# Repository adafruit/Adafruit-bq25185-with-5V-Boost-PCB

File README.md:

## Adafruit bq25185 USB - DC - Solar Charger with 5V Boost Board PCB

<a href="http://www.adafruit.com/products/6106"><br/>
Click here to purchase one from the Adafruit shop</a>

PCB files for the Adafruit bq25185 USB - DC - Solar Charger with 5V Boost Board. 

Format is EagleCAD schematic and board layout
* https://www.adafruit.com/product/6106

### Description

We're always on the look out for better ways to make projects portable: being able to charge your battery in the most convenient manner will let projects run no matter what power is available. Then we added a power supply chip with it to let you run your project without a separate board. The result is the Adafruit bq25185 USB / DC / Solar Charger with 5V Boost Board!

It uses the new bq25185 is a nifty charger chip with fairly high charge current, power path support, and the ability to charge from USB, DC or solar power. It's also a great value, so it's a good upgrade from MCP73833 or MCP73831-based charger boards. The boost converter is the TPS61023, which will give up to 1 Amp output with good efficiency, to squeeze the most power possible out of your battery.

This board is meant to be everything you need to power your 5V electronics: simply connect a 500mAh or larger battery to the JST PH 2-pin port, then charge it when you can from USB or DC/solar. At the other end is a terminal block which will provide the 5V output from the boost converter. 

* USB Type C connector with 5.1k CC resistors so it will work with any computer or power supply to get 5V and up to 1A. Data lines available if needed, on the bottom breakout.
* Separate DC or Solar Input - Two pads on the edge can be used to connect a 5 ~ 18V power supply, which can be used instead of USB. If the input is a solar panel, the charging chip will adjust the current draw so that the voltage does not dip below the battery, thus optimizing the solar power input. No large capacitor needed to stabilize it, and you get near-MPPT capability without the cost and complexity of MPPT.
* Default charge rate of 1A, but you can cut the jumper on the back to set the rate to 500mA
* Power Path to Load - If the 5V load connector is drawing current while the USB / DC/Solar power is attached, it will default to drawing current from the charger and any left over current will go to the battery. That keeps your battery from constantly charging/discharging which will reduce the battery life.
* Regulated 5V Output - a boost converter will take the load output from the bq25185 and convert it to 5V at 1 Amp max load. Note the TP61023 cannot turn on/off high loads, it will stall over 200mA. That means its not going to like it if you have a high current load that instantly draws full current on power up, like a resistive dummy load. The vast number of microcontroller projects will start up with <200mA and then a half second later will turn on high current items like LEDs, motors, wifi/radios, or displays so the restriction won't affect it.
* Three Status LEDs - Orange Charging LED, red Fault LED, and Green 3.3V output LED.
* Enable pad - to disable the 5V boost converter.
* Mounting holes!

This board is pretty much plug-and-play. Change the charging jumper if you like, then connect your battery to the BATT port, and the 5V output goes to your circuit. You can monitor the voltage on the battery via the secondary pads on the bottom edge, if necessary.

To use with solar, pick up a 5~7V solar panel (using a higher voltage panel will only lose the extra voltage as heat so there's no benefit to going over 7V), and either cut the connector off to wire it directly, or use a 2.1mm adapter cable plus a 2.1mm terminal block to get two wires for the DC Input port.

If you need a board with higher charge current or a DC plug already on-board, check out the bq24074 which has up to 1.5A charge rate and a on-board 2.1mm DC jack. It doesn't have a boost converter but you could wire up the TPS61023 separately

### License

Adafruit invests time and resources providing this open source design, please support Adafruit and open-source hardware by purchasing products from [Adafruit](https://www.adafruit.com)!

Designed by Limor Fried/Ladyada for Adafruit Industries.

Creative Commons Attribution/Share-Alike, all text above must be included in any redistribution. 
See license.txt for additional details.

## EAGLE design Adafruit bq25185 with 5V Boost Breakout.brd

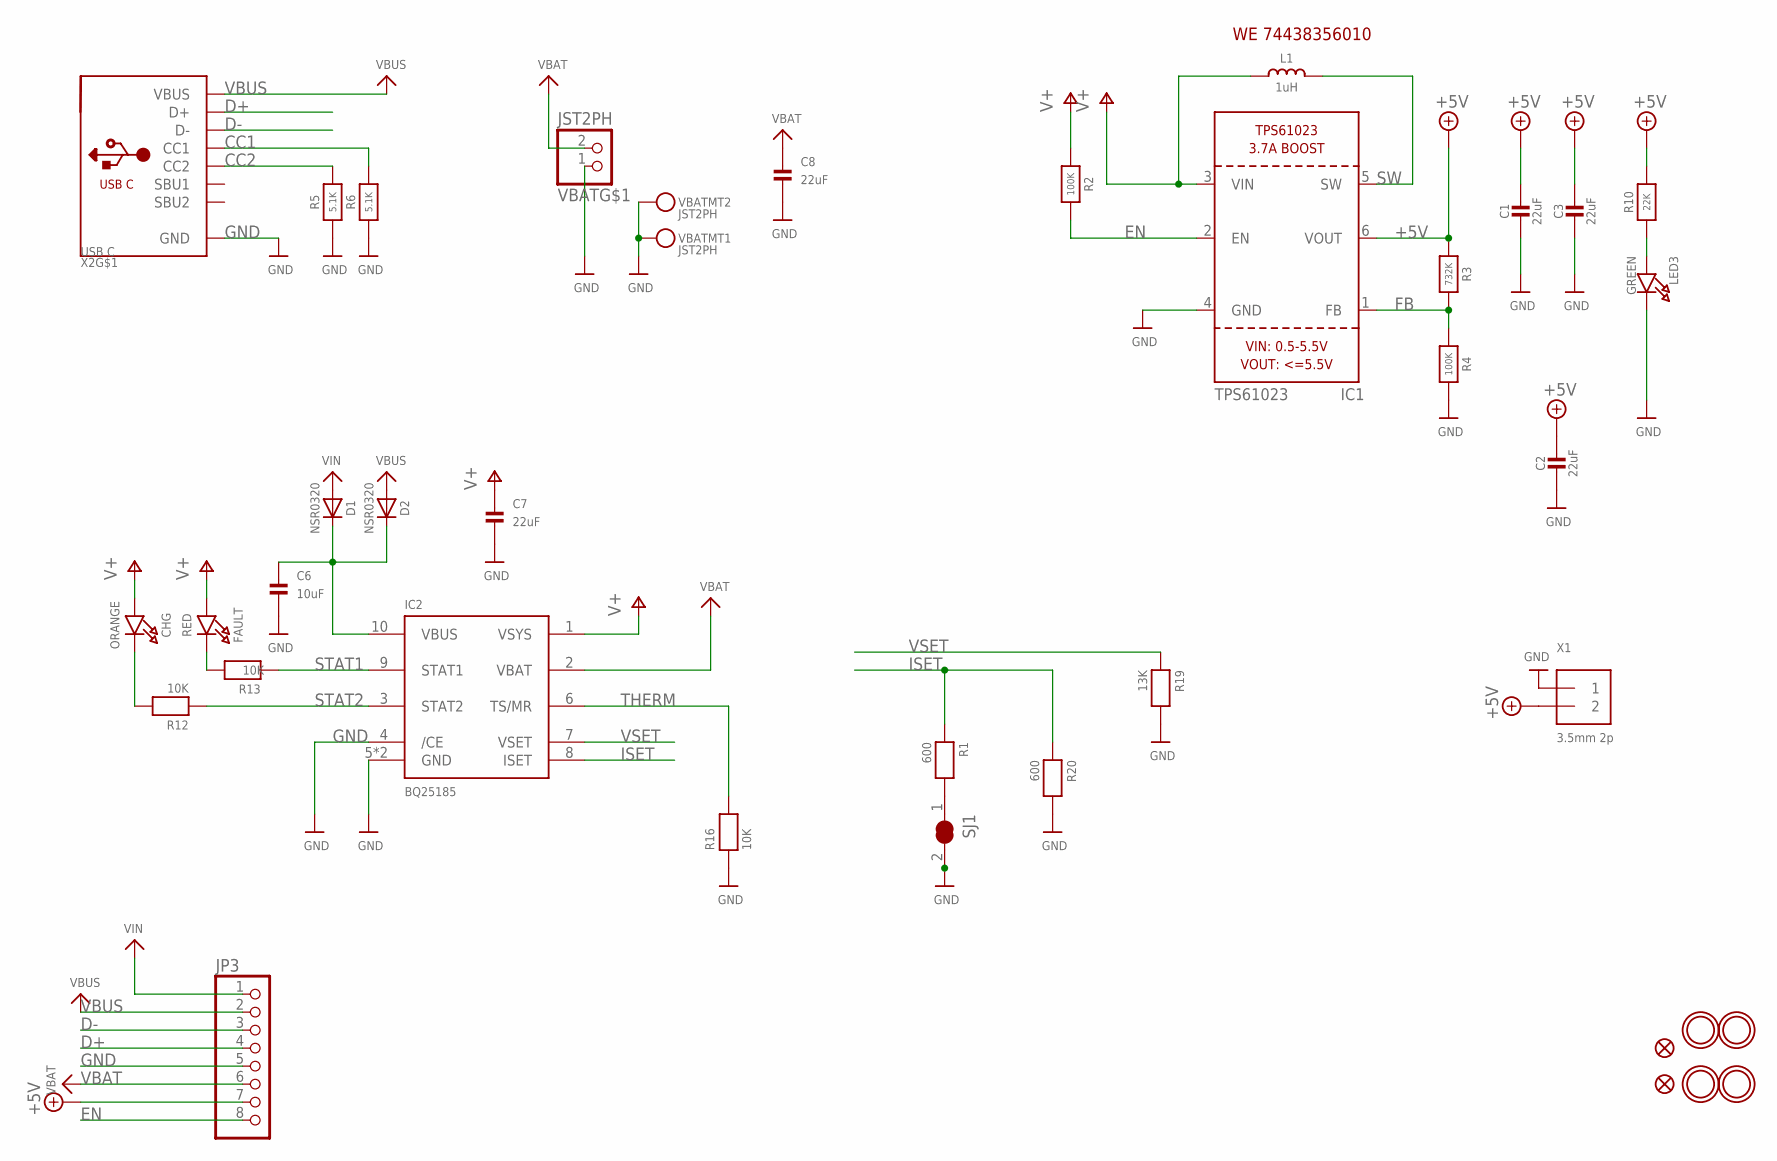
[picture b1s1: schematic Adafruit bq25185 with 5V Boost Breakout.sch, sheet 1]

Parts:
C1, C2, C3, C7, C8: 22uF; 0805-NO
C6: 10uF; 0805-NO
CHG: ORANGE; CHIPLED_0603_NOOUTLINE
D1, D2: NSR0320; SOD-323_MINI
FAULT: RED; CHIPLED_0603_NOOUTLINE
FID1, FID2: FIDUCIAL_0.5MM
IC1: TPS61023; SOT563
IC2: BQ25185; WSON10
JP3: HEADER-1X870MIL; 1X08_ROUND_70
L1: 1uH; INDUCTOR_5045_SMALLTABS
LED3: GREEN; CHIPLED_0603_NOOUTLINE
R1, R20: 600; _0402NO
R2, R4: 100K; _0402NO
R3: 732K; _0402NO
R5, R6: 5.1K; _0402NO
R10: 22K; _0402NO
R12, R13, R16: 10K; _0402NO
R19: 13K; _0402NO
SJ1: SOLDERJUMPER_CLOSED; SOLDERJUMPER_CLOSEDWIRE
U$9, U$10, U$11, U$12: MOUNTINGHOLE2.5; MOUNTINGHOLE_2.5_PLATED
VBAT: JST2PH; JSTPH2_BATT
X1: 3.5mm 2p; TERMBLOCK_1X2-3.5MM
X2: USB C; USB_C_CUSB31-CFM2AX-01-X

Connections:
+5V: C1.1, C2.1, C3.1, IC1.6 (VOUT), JP3.7, R3.1, R10.2, X1.2
CC1: R6.2, X2.A5 (CC1)
CC2: R5.2, X2.B5 (CC2)
D+: JP3.4, X2.A6 (D+), X2.B6 (D+)
D-: JP3.3, X2.A7 (D-), X2.B7 (D-)
EN: IC1.2 (EN), JP3.8, R2.2
FB: IC1.1 (FB), R3.2, R4.1
GND: C1.2, C2.2, C3.2, C6.2, C7.2, C8.2, IC1.4 (GND), IC2.4 (/CE), IC2.5 (GND), IC2.PAD (GND), JP3.5, LED3.C, R4.2, R5.1, R6.1, R16.1, R19.2, R20.2, SJ1.2, VBAT.1, VBAT.NC1, VBAT.NC2, X1.1, X2.A1B12 (GND), X2.B1A12 (GND)
ISET: IC2.8 (ISET), R1.1, R20.1
unnamed: R1.2, SJ1.1
unnamed: C6.1, D1.C, D2.C, IC2.10 (VBUS)
unnamed: CHG.C, R12.2
unnamed: LED3.A, R10.1
unnamed: FAULT.C, R13.2
STAT1: IC2.9 (STAT1), R13.1
STAT2: IC2.3 (STAT2), R12.1
SW: IC1.5 (SW), L1.2
THERM: IC2.6 (TS/MR), R16.2
V+: C7.1, CHG.A, FAULT.A, IC1.3 (VIN), IC2.1 (VSYS), L1.1, R2.1
VBAT: C8.1, IC2.2 (VBAT), JP3.6, VBAT.2
VBUS: D2.A, JP3.2, X2.A4B9 (VBUS), X2.B4A9 (VBUS)
VIN: D1.A, JP3.1
VSET: IC2.7 (VSET), R19.1

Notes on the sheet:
WE 74438356010

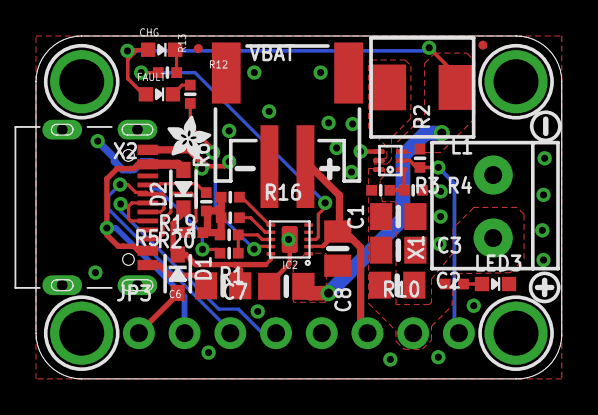
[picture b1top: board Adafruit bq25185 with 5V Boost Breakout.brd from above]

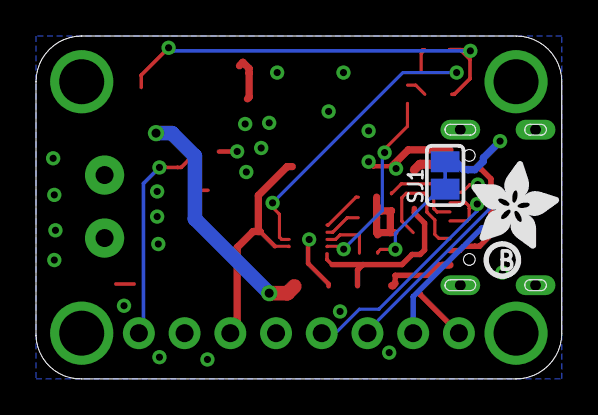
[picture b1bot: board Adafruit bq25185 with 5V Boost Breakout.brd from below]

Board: 2 copper layers, 29.2 x 19.1 mm, 66 parts (16 on the bottom side), 23 nets.

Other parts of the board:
PLABEL0: PLABEL0
PLABEL1: PLABEL1
PLABEL2: PLABEL2
PLABEL3: PLABEL3
PLABEL4: PLABEL4
PLABEL5: PLABEL5
PLABEL6: PLABEL6
PLABEL7: PLABEL7
PLABEL8: PLABEL8
PLABEL9: PLABEL9
PLABEL10: PLABEL10
PLABEL12: PLABEL12
PLABEL13: PLABEL13
PLABEL16: PLABEL16
PLABEL17: PLABEL17
PLABEL18: PLABEL18
PLABEL19: PLABEL19
PLABEL20: PLABEL20
PLABEL21: PLABEL21
PLABEL22: PLABEL22
PLABEL23: PLABEL23
PLABEL24: PLABEL24
PLABEL25: PLABEL25
PLABEL26: PLABEL26
U$2: PCBFEAT-REV-040
U$3: SYMBOL_PLUS
U$4: SYMBOL_MINUS
U$26: ADAFRUIT_5MM
U$34: ADAFRUIT_2.5MM

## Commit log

2024-12-04 cookiecutter

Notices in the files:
parts and their libraries:
microbuilder: This work is placed in the public domain, and may be freely used for commercial and non-commercial work with the following conditions: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
